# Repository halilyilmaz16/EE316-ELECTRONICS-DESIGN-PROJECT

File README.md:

# Capacitive Water Level Controller

An analog closed-loop water level control system designed and implemented
for the EE 316 Electronic Design Project (project P1) at İzmir Institute of Technology, June 2026.

The system detects liquid-level variations using a custom cylindrical
capacitive sensor. The sensor output is processed through phase detection,
filtering, amplification, error generation, and PWM stages. The resulting
PWM signal controls a submersible DC water pump through an L298N motor driver.
When the water level is low the pump runs at full duty cycle; as the level rises
the duty cycle drops and the pump switches off.

## How it works

```mermaid
flowchart LR
    P["Capacitive probe<br/>(aluminum strips on plastic tube)"] --> X["XOR phase detector<br/>(74LS86)"]
    O["555 astable oscillator<br/>(reference clock)"] --> P
    O --> X
    X --> F["RC low-pass filter"]
    F --> A["Offset amplifier<br/>(LM358)"]
    A --> E["Error amplifier<br/>Vref − Vactual"]
    R["Reference level<br/>(potentiometer)"] --> E
    Q["Square wave<br/>(74LS74, fclk/4)"] --> T["Triangular wave<br/>(RC integrator)"]
    O --> Q
    E --> W["PWM comparator<br/>Verror vs Vtri"]
    T --> W
    W --> D["L298N driver"] --> U["Submersible DC pump"]
    D -.-> I["Current sense<br/>(ACS712)"]
```

| Stage | What it does | Main parts |
|---|---|---|
| Probe | Capacitance changes linearly with water height (design range: 5–15 cm of water, 213–661 pF) | Aluminum strips, plastic tube, 3D-printed frame |
| Oscillator | Generates the reference clock | 555 timer, astable mode |
| Phase detector | Compares the clock with the phase-shifted clock from the probe; pulse width tracks the level | 74LS86 (XOR) |
| Filter and offset | Turns the pulses into a DC level and shifts it into the control range | RC filter, LM358 |
| Error amplifier | Compares the measured level with the user-set reference | LM358, potentiometer |
| Triangular carrier | Divides the clock by 4 and integrates it into a triangle wave | 74LS74, RC network |
| PWM generator | Duty cycle follows the error: low water gives a fast pump | Comparator |
| Motor stage | Drives the pump with overcurrent protection | L298N, ACS712 |

## Key Features

- Custom cylindrical capacitive water-level sensor
- 555-based oscillator
- XOR-based phase detection
- RC filtering and LM358 signal amplification
- Adjustable reference water level
- PWM-based pump speed control
- Motor overcurrent protection
- LTspice simulation and real-world circuit testing

## Repository layout

| Path | Contents |
|---|---|
| `Water level project.kicad_*` | KiCad schematic, PCB and project files |
| `ltspice/` | LTspice schematic ([`EE316_30.06.2026.asc`](ltspice/EE316_30.06.2026.asc)) and a zip with the ACS712 model and simulation outputs |
| `datasheets/` | Datasheets: ACS712, BC847C, HD74LS74A, HD74LS86, L298, LM358, NE555 |
| `reports_and_demonstration/` | Final report (26 pages) and demonstration slides |
| `report.txt` | Log produced when the PCB was updated from the schematic in KiCad |

## KiCad design review (November 2026)

> **⚠️ Not tested in hardware.** The KiCad schematic and PCB in this repository were revised after the
> project and checked only with KiCad's electrical rules check (ERC: 0 errors) and design rules check
> (DRC: 0 errors, 0 unconnected). The revised board has **not been manufactured or tested**. The
> bench prototype in the report was built on a breadboard, not from this PCB.

Changes compared with the original KiCad files:

| Change | Why |
|---|---|
| Power units added for U2/U4 (LM358) and U6 (LM393); pins 8/4 now on +5V/GND | Their power pins were unconnected on the PCB, so the op-amps had no supply |
| Unused op-amp (U4B), comparator (U6B) and XOR gates (U3B–D) terminated | Floating inputs can oscillate and draw extra current |
| 100 nF decoupling capacitor added at every IC (C8–C13) | The board had no decoupling |
| R17 10 kΩ pull-up on the LM393 output (J2) | The LM393 has an open-collector output, so it could never drive high |
| RV1 pin 1 tied to GND; C5 moved to the wiper as a filter | One end of the pot was unconnected, so the reference stayed fixed at 2.5 V |
| GND copper pour on the bottom layer; PWR_FLAG symbols added | Grounding and ERC |

## Documents

- [Final report](reports_and_demonstration/Water_Level_Controller_final_report.pdf): design, revision history, challenges
- [Demonstration slides](reports_and_demonstration/Water_Level_Controller.pdf): block-by-block summary of the design

## Team

- Hasan Veysel Tutar: capacitor design and manufacturing, real circuit assembly, testing and troubleshooting
- Halil Yılmaz: simulations and circuit building assistance
- Doruk Öğüt: simulations and circuit building assistance

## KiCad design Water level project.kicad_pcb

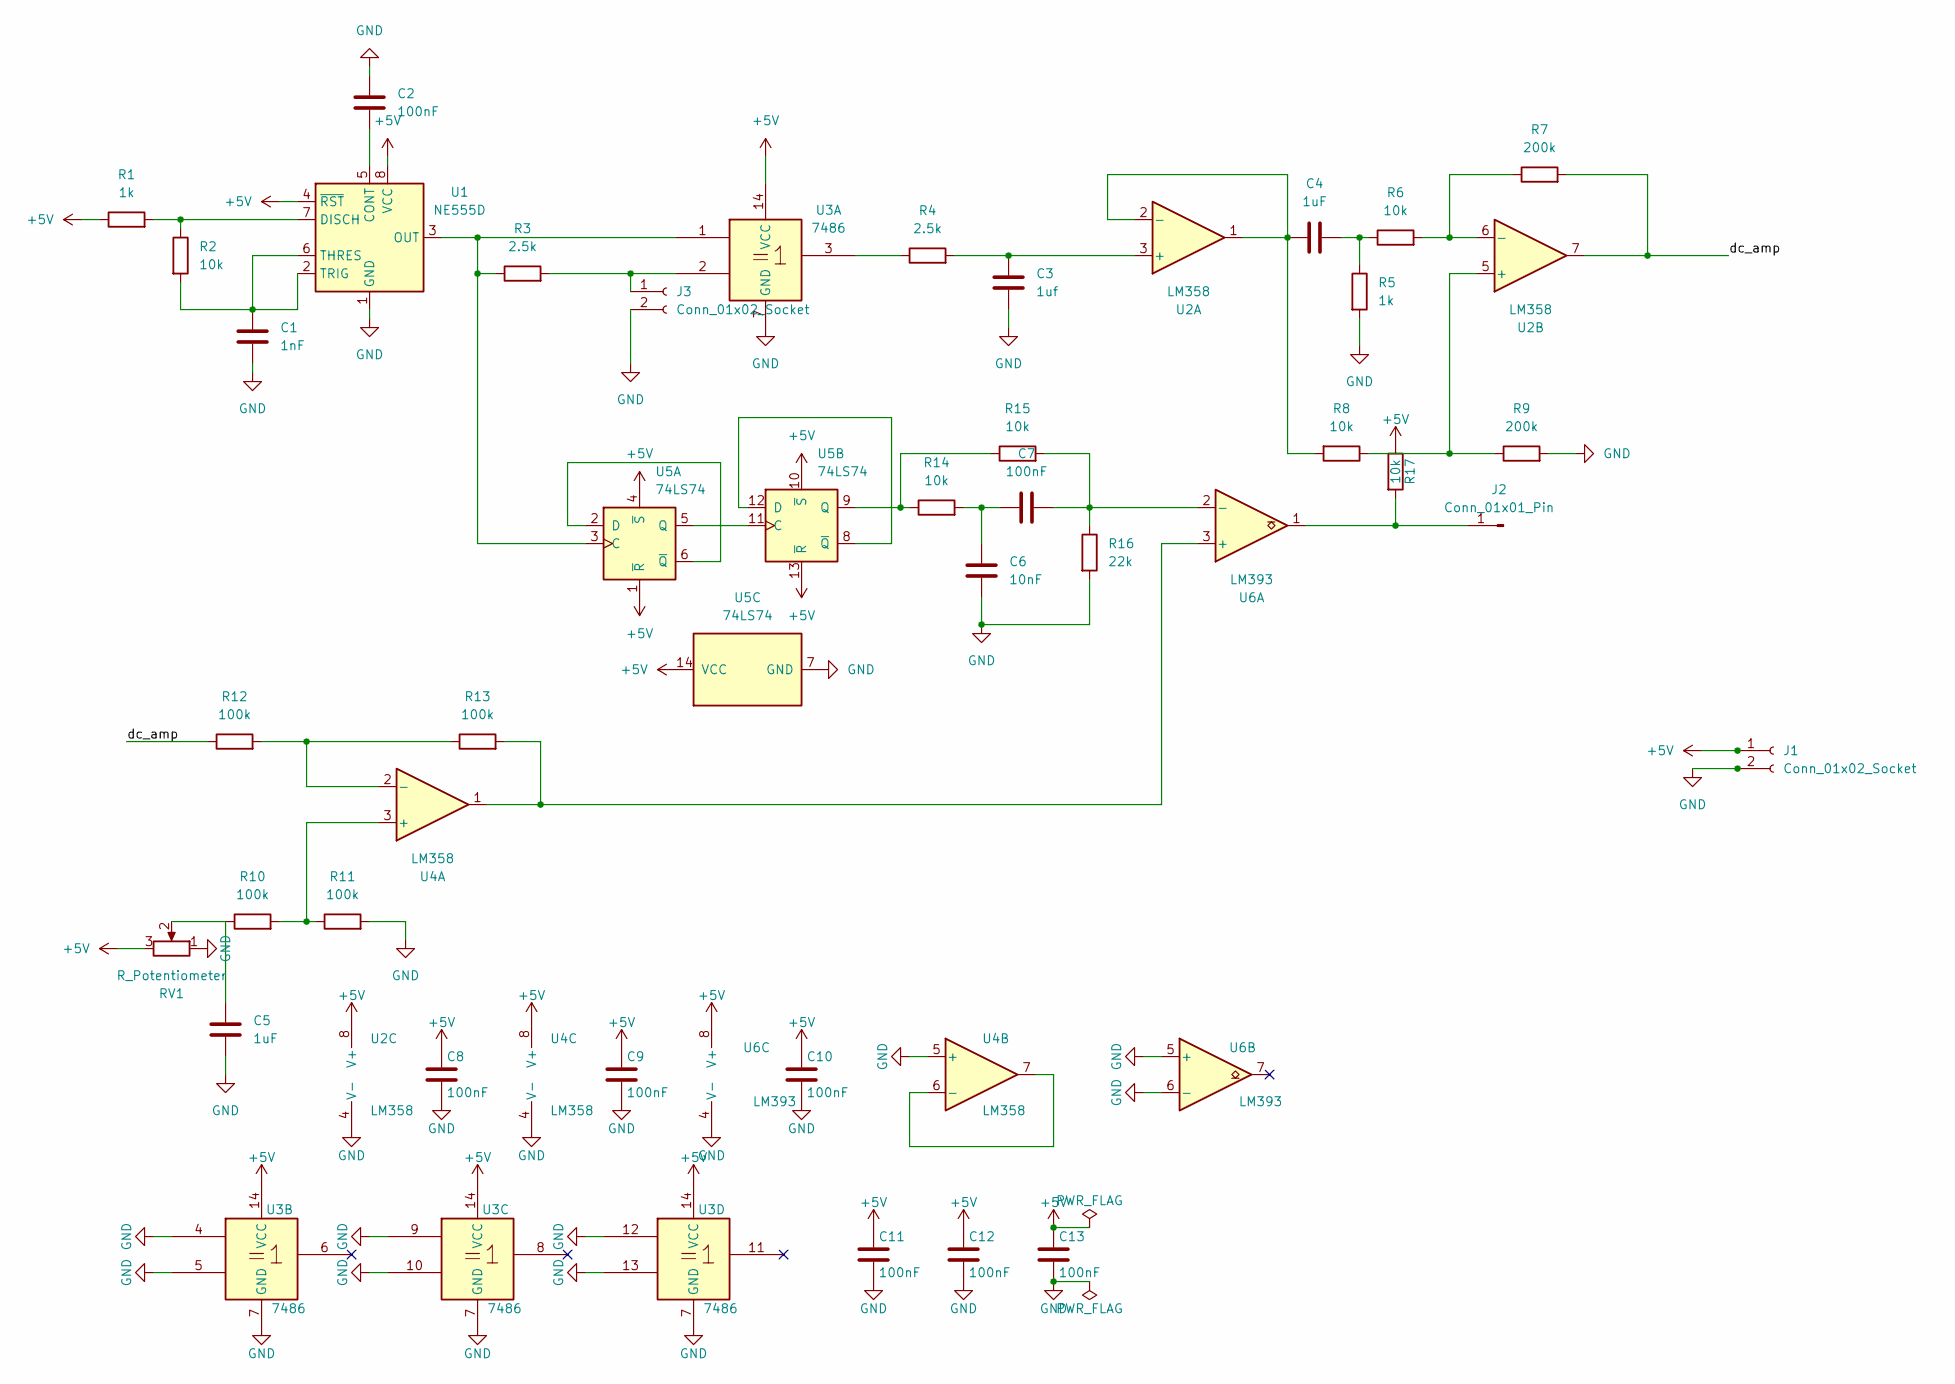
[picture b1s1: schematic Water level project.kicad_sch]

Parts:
C1: 1nF; C_Disc_D4.3mm_W1.9mm_P5.00mm
C2, C7, C8, C9, C10, C11, C12, C13: 100nF; C_Disc_D5.0mm_W2.5mm_P5.00mm
C3: 1uf; CP_Radial_D5.0mm_P2.50mm
C4, C5: 1uF; CP_Radial_D5.0mm_P2.50mm
C6: 10nF; C_Disc_D4.3mm_W1.9mm_P5.00mm
J1, J3: Conn_01x02_Socket; PinSocket_1x02_P2.54mm_Vertical
J2: Conn_01x01_Pin; PinSocket_1x01_P2.54mm_Vertical
R1, R5: 1k; R_Axial_DIN0207_L6.3mm_D2.5mm_P7.62mm_Horizontal
R2, R6, R8, R14, R15, R17: 10k; R_Axial_DIN0207_L6.3mm_D2.5mm_P7.62mm_Horizontal
R3, R4: 2.5k; R_Axial_DIN0207_L6.3mm_D2.5mm_P7.62mm_Horizontal
R7, R9: 200k; R_Axial_DIN0207_L6.3mm_D2.5mm_P7.62mm_Horizontal
R10, R11, R12, R13: 100k; R_Axial_DIN0207_L6.3mm_D2.5mm_P7.62mm_Horizontal
R16: 22k; R_Axial_DIN0207_L6.3mm_D2.5mm_P7.62mm_Horizontal
RV1: R_Potentiometer; Potentiometer_Piher_PC-16_Single_Vertical
U1: NE555D; DIP-8_W7.62mm
U2, U4: LM358; DIP-8_W7.62mm
U3: 7486; DIP-14_W7.62mm
U5: 74LS74; DIP-14_W7.62mm
U6: LM393; DIP-8_W7.62mm

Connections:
+5V: C8.1, C9.1, C10.1, C11.1, C12.1, C13.1, J1.1, R1.1, R17.1, RV1.3, U1.4 (~RST), U1.8 (VCC), U2.8 (V+), U3.14 (VCC), U4.8 (V+), U5.1 (~R), U5.4 (~S), U5.10 (~S), U5.13 (~R), U5.14 (VCC), U6.8 (V+)
/dc_amp: R7.2, R12.1, U2.7
GND: C1.2, C2.1, C3.2, C5.2, C6.2, C8.2, C9.2, C10.2, C11.2, C12.2, C13.2, J1.2, J3.2, R5.2, R9.2, R11.2, R16.2, RV1.1, U1.1 (GND), U2.4 (V-), U3.4, U3.5, U3.7 (GND), U3.9, U3.10, U3.12, U3.13, U4.4 (V-), U4.5 (+), U5.7 (GND), U6.4 (V-), U6.5 (+), U6.6 (-)
unnamed: C4.2, R5.1, R6.1
unnamed: C5.1, R10.1, RV1.2
unnamed: C6.1, C7.1, R14.2
unnamed: J2.1 (Pin_1_1), R17.2, U6.1
unnamed: J3.1, R3.2, U3.2
unnamed: R4.1, U3.3
unnamed: C2.2, U1.5 (CONT)
unnamed: R1.2, R2.1, U1.7 (DISCH)
unnamed: R3.1, U1.3 (OUT), U3.1, U5.3 (C)
unnamed: C1.1, R2.2, U1.2 (TRIG), U1.6 (THRES)
unnamed: C3.1, R4.2, U2.3 (+)
unnamed: C4.1, R8.2, U2.1, U2.2 (-)
unnamed: R8.1, R9.1, U2.5 (+)
unnamed: R6.2, R7.1, U2.6 (-)
unnamed: R10.2, R11.1, U4.3 (+)
unnamed: R12.2, R13.1, U4.2 (-)
unnamed: U4.6 (-), U4.7
unnamed: U5.2 (D), U5.6 (~Q)
unnamed: U5.5 (Q), U5.11 (C)
unnamed: U5.8 (~Q), U5.12 (D)
unnamed: R14.1, R15.1, U5.9 (Q)
unnamed: R13.2, U4.1, U6.3 (+)
unnamed: C7.2, R15.2, R16.1, U6.2 (-)

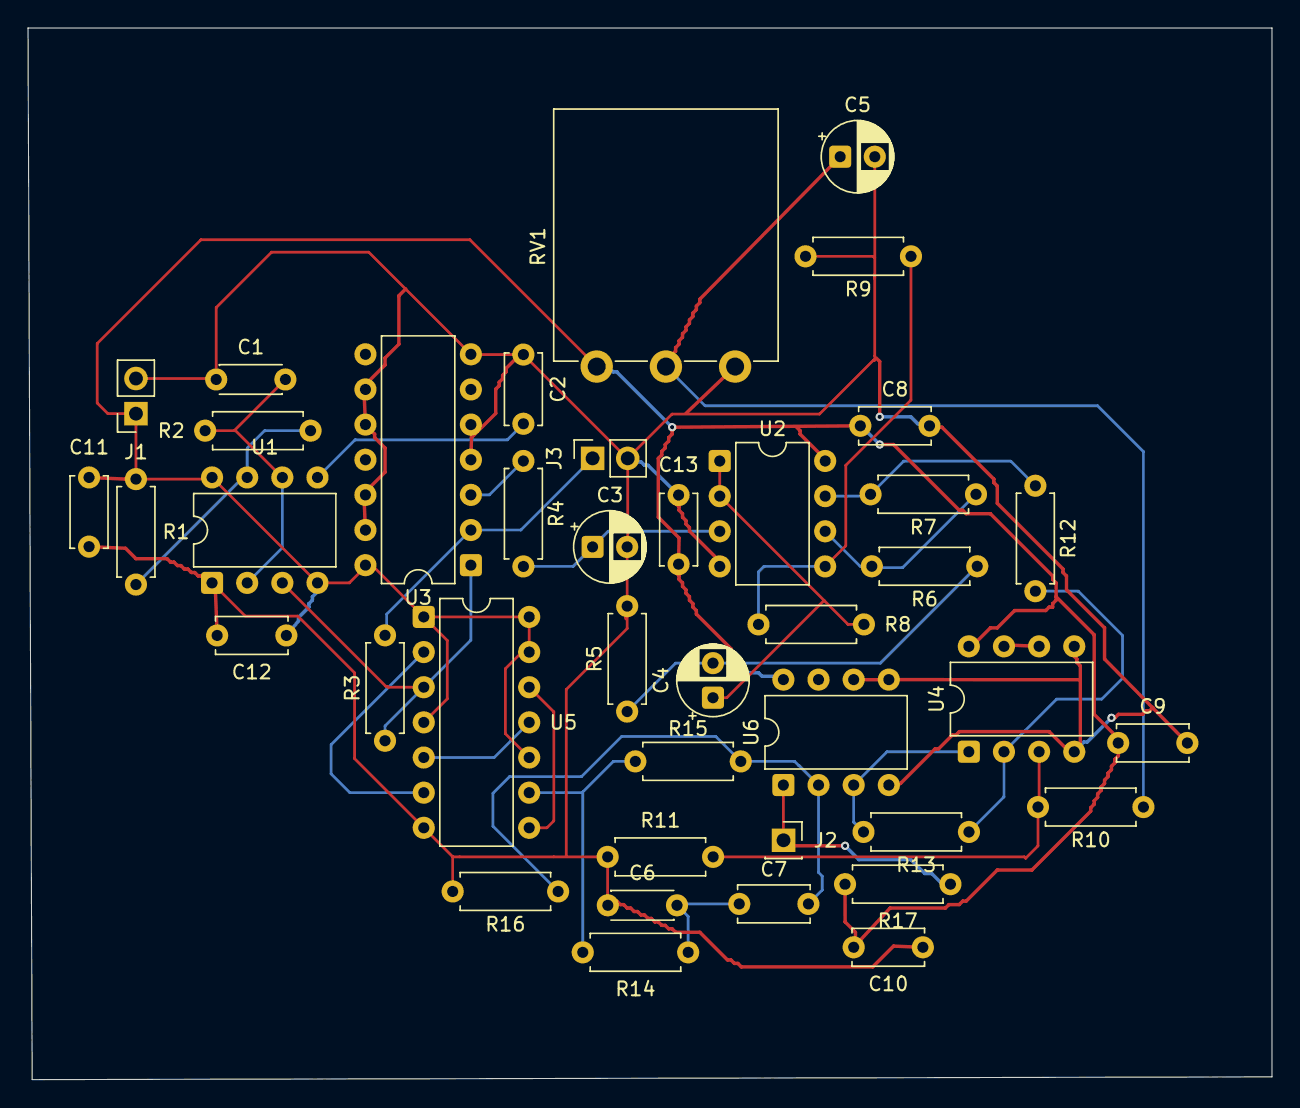
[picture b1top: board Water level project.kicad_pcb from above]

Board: 2 copper layers, 89.9 x 76.0 mm, 40 parts (0 on the bottom side), 26 nets.
